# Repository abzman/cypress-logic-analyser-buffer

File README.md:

# cypress-logic-analyser-buffer

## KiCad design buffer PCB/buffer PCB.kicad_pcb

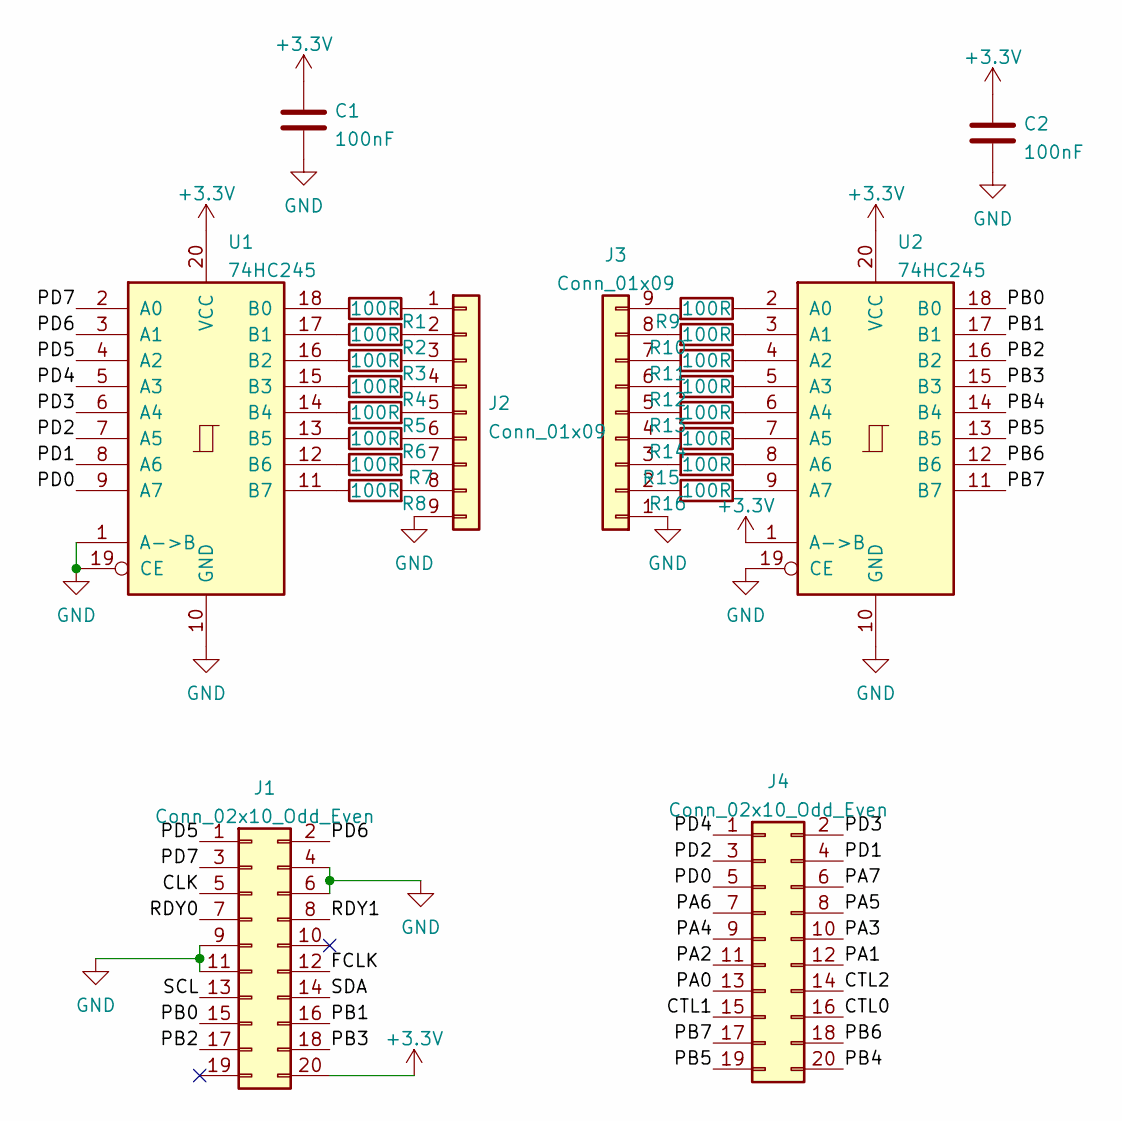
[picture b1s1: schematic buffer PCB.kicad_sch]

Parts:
C1, C2: 100nF; C_0603_1608Metric
J1, J4: Conn_02x10_Odd_Even; PinHeader_2x10_P2.54mm_Vertical
J2, J3: Conn_01x09; PinHeader_1x09_P2.54mm_Horizontal
R1, R2, R3, R4, R5, R6, R7, R8, R9, R10, R11, R12, R13, R14, R15, R16: 100R; R_0603_1608Metric
U1, U2: 74HC245; DIP-20_W7.62mm

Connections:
+3V3: C1.1, C2.1, J1.20, U1.20 (VCC), U2.1 (A->B), U2.20 (VCC)
/CLK: J1.5
/CTL0: J4.16
/CTL1: J4.15
/CTL2: J4.14
/FCLK: J1.12
/PA0: J4.13
/PA1: J4.12
/PA2: J4.11
/PA3: J4.10
/PA4: J4.9
/PA5: J4.8
/PA6: J4.7
/PA7: J4.6
/PB0: J1.15, U2.18 (B0)
/PB1: J1.16, U2.17 (B1)
/PB2: J1.17, U2.16 (B2)
/PB3: J1.18, U2.15 (B3)
/PB4: J4.20, U2.14 (B4)
/PB5: J4.19, U2.13 (B5)
/PB6: J4.18, U2.12 (B6)
/PB7: J4.17, U2.11 (B7)
/PD0: J4.5, U1.9 (A7)
/PD1: J4.4, U1.8 (A6)
/PD2: J4.3, U1.7 (A5)
/PD3: J4.2, U1.6 (A4)
/PD4: J4.1, U1.5 (A3)
/PD5: J1.1, U1.4 (A2)
/PD6: J1.2, U1.3 (A1)
/PD7: J1.3, U1.2 (A0)
/RDY0: J1.7
/RDY1: J1.8
/SCL: J1.13
/SDA: J1.14
GND: C1.2, C2.2, J1.4, J1.6, J1.9, J1.11, J2.9, J3.1, U1.1 (A->B), U1.10 (GND), U1.19 (CE), U2.10 (GND), U2.19 (CE)
unnamed: J2.1, R1.2
unnamed: J2.2, R2.2
unnamed: J2.3, R3.2
unnamed: J2.4, R4.2
unnamed: J2.5, R5.2
unnamed: J2.6, R6.2
unnamed: J2.7, R7.2
unnamed: J2.8, R8.2
unnamed: J3.2, R16.2
unnamed: J3.3, R15.2
unnamed: J3.4, R14.2
unnamed: J3.5, R13.2
unnamed: J3.6, R12.2
unnamed: J3.7, R11.2
unnamed: J3.8, R10.2
unnamed: J3.9, R9.2
unnamed: R1.1, U1.18 (B0)
unnamed: R2.1, U1.17 (B1)
unnamed: R3.1, U1.16 (B2)
unnamed: R4.1, U1.15 (B3)
unnamed: R5.1, U1.14 (B4)
unnamed: R6.1, U1.13 (B5)
unnamed: R7.1, U1.12 (B6)
unnamed: R8.1, U1.11 (B7)
unnamed: R9.1, U2.2 (A0)
unnamed: R10.1, U2.3 (A1)
unnamed: R11.1, U2.4 (A2)
unnamed: R12.1, U2.5 (A3)
unnamed: R13.1, U2.6 (A4)
unnamed: R14.1, U2.7 (A5)
unnamed: R15.1, U2.8 (A6)
unnamed: R16.1, U2.9 (A7)

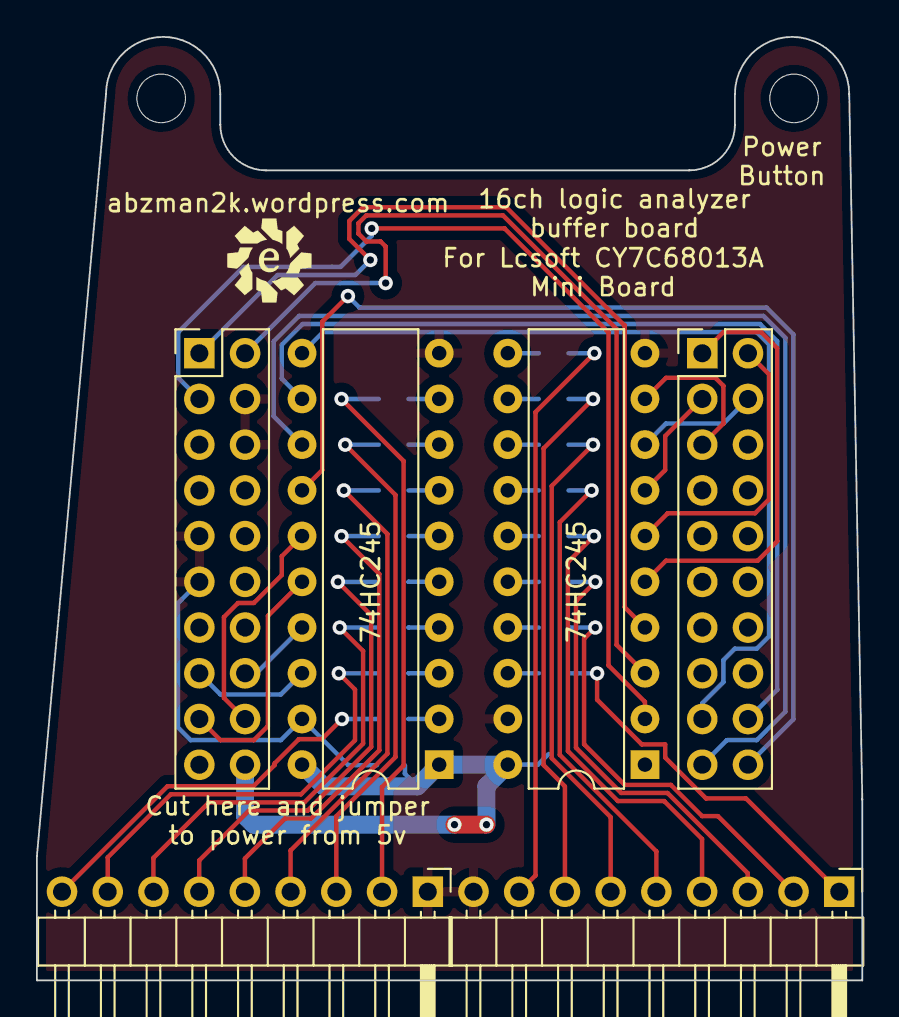
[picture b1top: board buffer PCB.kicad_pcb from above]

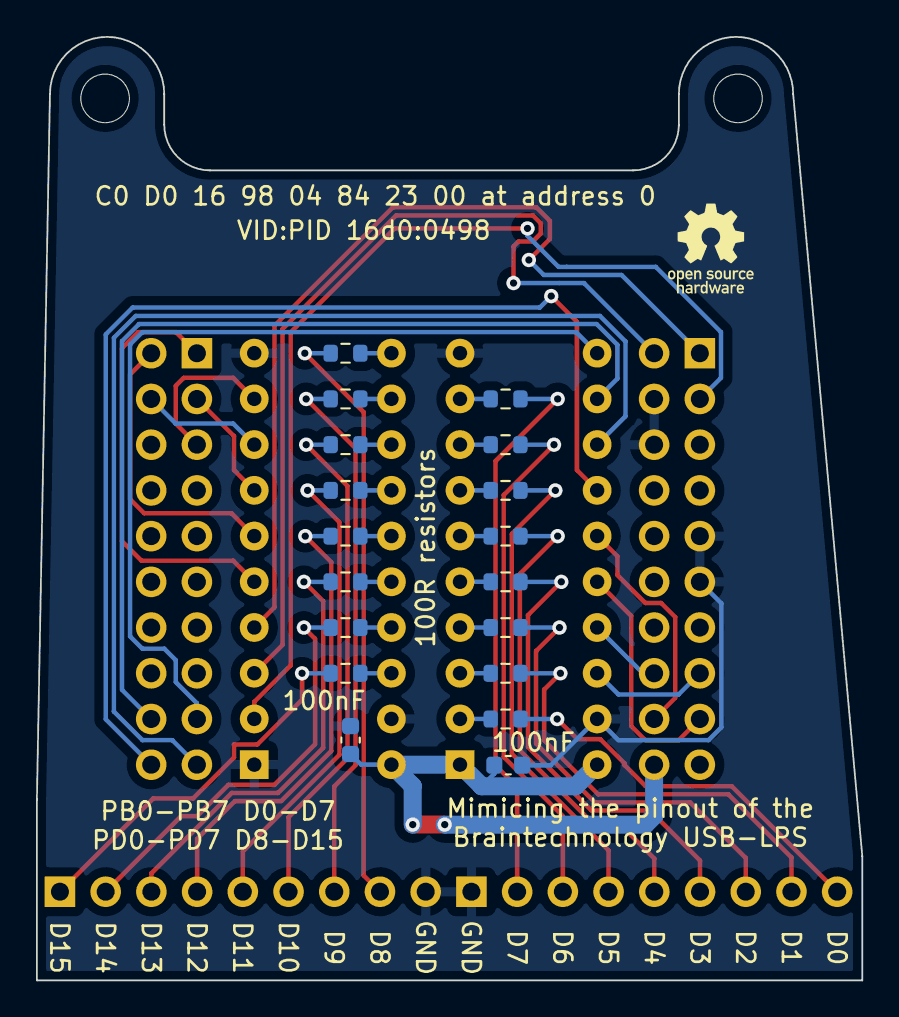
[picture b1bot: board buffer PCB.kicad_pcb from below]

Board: 2 copper layers, 45.9 x 52.4 mm, 24 parts (18 on the bottom side), 50 nets.

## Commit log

2022-03-13 generated gerbers
2022-03-14 gerber zip
2022-03-29 updated for different board power pinout and proper hole locations
2022-04-18 backed up eproms from board
2022-11-25 added gitignore
